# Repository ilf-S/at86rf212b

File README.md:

##
Kicad project files for a 2 layer PCB with AT86RF212B transceiver. The board uses separated digital and analog ground planes on a 2 layer PCB design. Board has not been tested yet, so use with caution.

##
1. 2 Layer design
2. 4 Ground planes: Digital, Analog, Xtal & RF
	* Digital handles all signals like SPI connection, IRQ, etc.
	* Analog is mostly for things connected to the RF/Xtal, etc. but is confined bellow the IC QFN package. Consult the documentation, all analog ground pins are connected to the pads bellow the QFN.
	* The RF is a separate plane connected to the IC by the two analog GND pins surrounding the RF_P/RF_N pins. Again consult the documentation
	* The Xtal GND plane is connected to the IC with a single Analog GND pin and is hard grounded with via stitches. This hopefully will help with interference with the nearby IRQ pin. Capacitance could be an issue, though, might need some tweaking.

##
The rest is straight forward. Just follow the AT86RF212B Atmel SpecSheet.

##
**Still not tested!**

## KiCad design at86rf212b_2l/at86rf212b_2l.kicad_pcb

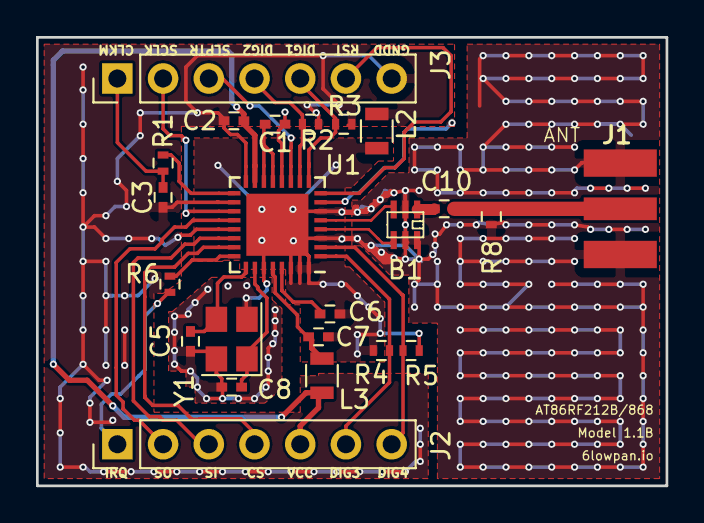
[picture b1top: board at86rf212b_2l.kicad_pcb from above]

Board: 2 copper layers, 35.0 x 24.9 mm, 23 parts (0 on the bottom side), 26 nets.

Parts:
B1: BALUN
C1, C2, C6, C7: 1uF; C_0402
C3: 2.2pF; C_0402
C5, C8: 10pF; C_0402
C10: 100pF; C_0402
J1: ANT; SMA_EDGELAUNCH
J2, J3: Conn_01x07; Pin_Header_Straight_1x07_Pitch2.54mm
L2: FB2; R_0805
L3: FB1; R_0805
R1: 470; R_0402
R2, R3, R4, R5: 0; R_0402
R6: 22; R_0402
R8: 10k; R_0402
U1: AT86RF212B; QFN-32-1EP_5x5mm_Pitch0.5mm
Y1: 16.0Mhz; Crystal_SMD_3225-4pin_3.2x2.5mm

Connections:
/CLKM: C3.1, J3.1, R1.1
/CS: J2.4, U1.23
/DIG1: J3.5, R3.2, U1.9
/DIG2: J3.4, R2.2, U1.10
/DIG3: J2.6, R4.2, U1.1
/DIG4: J2.7, R5.2, U1.2
/IRQ: J2.1, R6.2
/MISO: J2.2, U1.20
/MOSI: J2.3, U1.22
/RST: J3.6, U1.8
/SCLK: J3.2, U1.19
/SLPTR: J3.3, U1.11
GND: B1.2, B1.5, B1.6, C5.1, C6.1, C7.1, C8.1, J1.GND, L2.1, R4.1, R5.1, R8.1, U1.3, U1.6, U1.27, U1.30, U1.31, U1.32, U1.33, Y1.2, Y1.4
GNDPWR: C1.2, C2.2, C3.2, J3.7, L2.2, R2.1, R3.1, U1.7, U1.12, U1.16, U1.18, U1.21
unnamed: B1.1, C10.2
unnamed: B1.3, U1.5
unnamed: B1.4, U1.4
unnamed: C1.1, U1.13, U1.14
unnamed: C5.2, U1.25, Y1.3
unnamed: C6.2, U1.29
unnamed: C8.2, U1.26, Y1.1
unnamed: C10.1, J1.P, R8.2
unnamed: R1.2, U1.17
unnamed: R6.1, U1.24
VCC: C2.1, J2.5, L3.2, U1.15
VDD: C7.2, L3.1, U1.28

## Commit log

2017-10-27 Initial import of Kicad project files for AT86RF212B transceiver
2017-10-27 Initial README
2017-10-28 Moving the kicad project files in a separate directory. Adding directory with gerber plots
2017-10-28 clean up the root directory
2017-10-28 further clean-up
2017-10-28 clean up
2017-10-28 Fix the Analog and Digital Ground connections for pins DIG1,DIG2,DIG3,DIG4. Were swapped in the previous version
2017-10-28 latest fixes on vias, layers, pads for the SMA antenna and the edge cuts area.
2017-10-28 minor move of some vias around the antenna feed line
2017-11-01 Latest commits. Splitting ground planes in 4: Digital, Analog, Xtal & RF. All 4 connected in the QFN package, essentially following a "star" formation. Spacing is around 12 mils, so most fabs can han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
    Also latest Gerber plots in the plots directory.
2017-11-01 More explanation around the design and the current state.
2017-11-01 Syntax clean up
2017-11-01 Syntax clean up of the readme
2017-11-01 Syntax
2017-12-01 AT86RFR212b package, mistakenly used QFP instaed of the proper QFN 32 bit package. Now fixed. That lead to some minor tweaks and fixes around the ground planes. Also moved the resistor for the IRQ, e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
